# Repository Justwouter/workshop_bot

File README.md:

Welcome to the Acrobot Workshop bot

This is a small version of the [Acrobot](https://Acrobot.nl), a simple but expressive robot acrobat with 4 joints. It is easy to animate by using [Bottango](https://www.bottango.com/).

The project was developed by [Daniel Simu](https://danielsimu.com), with funding and support from [Creative Coding Utrecht](https://creativecodingutrecht.nl/).
Additional materials were sponsored by [DFRobot](https://www.dfrobot.com/),  [Fillamentum](https://fillamentum.com/) and [Tinytronics](https://www.tinytronics.nl/en/)

https://github.com/user-attachments/assets/d1673c57-b2f6-4ec9-994d-3f826fc23f9e

# Required materials

For a workshop you need 3 things:
- Workshop bot
- ESP-NOW dongle
- Computer with Bottango software
  
Typically 2 - 3 participants can use 1 robot kit.

## Bottango

- The Bottango project file can be found in this repo.
- The ESP-NOW dongle is flashed with the BottangoArduinoDriver in parent mode, and connected to the computer running Bottango
- The ESP32 on the robot is running the BottangoArduinoDriver in child  mode

Make sure to update the child code with the mac address of the parent, and in Bottango enter the mac address of the child and the COM port in the hardware settings.

## Building the robot

3d model files, schematics and pcb gerber files are in the repo.

- The body consists of 2 3d printed halves, in PLA
- The shoulders, hips, hands and feet are best printed of TPU98A from [Fillamentum](https://fillamentum.com/)
- The motors are ideally 6Kg 300° Clutch Servos from [DFRobot](https://www.dfrobot.com/) 
- The ideal ESP32 for the robot is this [TTGO-T18](https://github.com/LilyGO/TTGO-T-Cell), which comes with a battery holder and a button. You can get these from [Tinytronics](https://www.tinytronics.nl/en/development-boards/microcontroller-boards/with-wi-fi/lilygo-ttgo-t-cell-esp32-with-3-way-button-and-18650-battery-holder)
  - I recommend squeezing a protected 18650 cell into the battery holder, the holder terminals may need to be bent to fit this.
- The dongle can be any standard ESP32, I use a Pico-d4 with a usb plug connector mounted on it.
- You can solder the electronics together on a perfboard, or fabricate the pcb.
- You will need 2 small screws to hold the ESP(2x6mm works well), and 3 M3 nuts and M3x30mm bolts to close the case.
- 16mm alluminium tubes are used for arms and legs, recommended sizes are 190mm and 290mm

# Todo

- Write detailed instructions about how to fabricate and assemble the motors
- Write workshop instructions
- Improve robot design

# License

This project is shared under the Creative Commons Attribution 4.0 International license. 

We're open to consider other licenses that are better suited for open hardware design.

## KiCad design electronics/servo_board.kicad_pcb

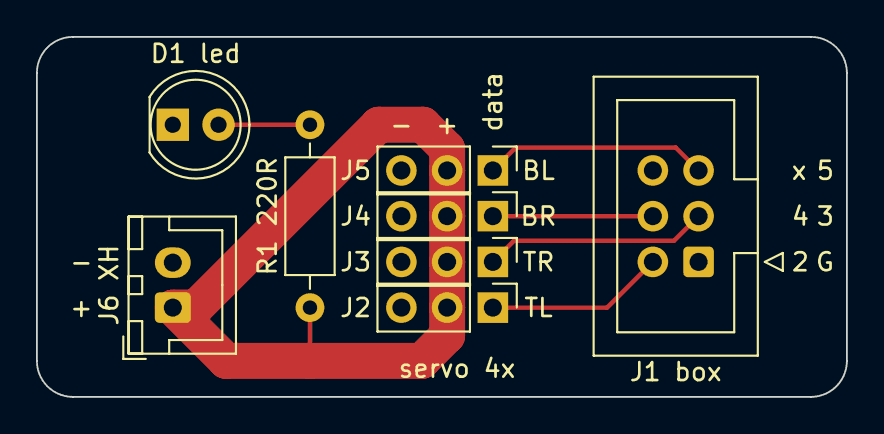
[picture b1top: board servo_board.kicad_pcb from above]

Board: 2 copper layers, 45.0 x 20.0 mm, 8 parts (0 on the bottom side), 7 nets.

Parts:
D1 led: LED; LED_D5.0mm
J1 box: Conn_02x03_Odd_Even; IDC-Header_2x03_P2.54mm_Vertical
J2, J3, J4, J5: Conn_01x03; PinHeader_1x03_P2.54mm_Vertical
J6 XH: Conn_01x02; JST_XH_B2B-XH-A_1x02_P2.50mm_Vertical
R1 220R: 220R; R_Axial_DIN0207_L6.3mm_D2.5mm_P10.16mm_Horizontal

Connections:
/Data_BL: J1 box.5, J5.1
/Data_BR: J1 box.4, J4.1
/Data_TL: J1 box.2, J2.1
/Data_TR: J1 box.3, J3.1
GND: D1 led.1 (K), J1 box.1, J2.3, J3.3, J4.3, J5.3, J6 XH.2
unnamed: D1 led.2 (A), R1 220R.2
VDD: J2.2, J3.2, J4.2, J5.2, J6 XH.1, R1 220R.1

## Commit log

2025-02-25 new driver
2025-03-11 added pictures
2025-03-11 files v2
2025-03-13 fixing videoi?
2025-03-13 Different mp4 type now
2025-06-06 Restructure ino, add servo read
2025-06-06 Working wifi stuff
2025-06-13 Invert left motor, add wifi disconnect , fix normalizing servo
2025-06-13 Fuckery with servos
